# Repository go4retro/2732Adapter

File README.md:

# 2732Adapter
JEDEC 2732 to JEDEC 27XX(X) Adapter

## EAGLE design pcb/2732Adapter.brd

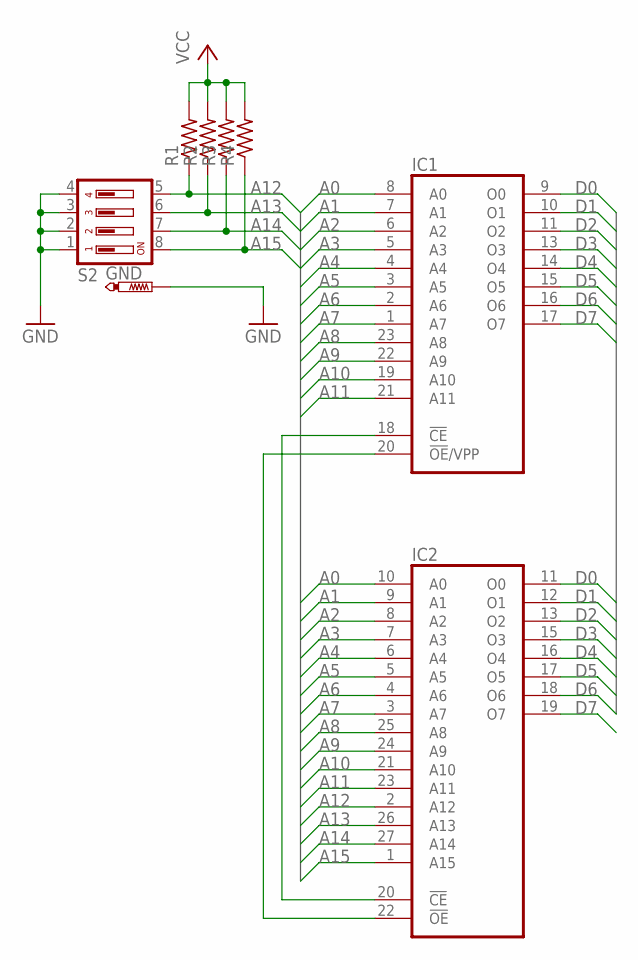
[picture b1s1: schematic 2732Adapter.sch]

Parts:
GND: PTR1B1,27; B1,27
IC1: 2732; DIL24
IC2: 27512; DIL28
R1, R2, R3, R4: R-US_0204/5; 0204/5
S2: DP04; DP-04

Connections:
A0: IC1.8 (A0), IC2.10 (A0)
A1: IC1.7 (A1), IC2.9 (A1)
A2: IC1.6 (A2), IC2.8 (A2)
A3: IC1.5 (A3), IC2.7 (A3)
A4: IC1.4 (A4), IC2.6 (A4)
A5: IC1.3 (A5), IC2.5 (A5)
A6: IC1.2 (A6), IC2.4 (A6)
A7: IC1.1 (A7), IC2.3 (A7)
A8: IC1.23 (A8), IC2.25 (A8)
A9: IC1.22 (A9), IC2.24 (A9)
A10: IC1.19 (A10), IC2.21 (A10)
A11: IC1.21 (A11), IC2.23 (A11)
A12: IC2.2 (A12), R1.1, S2.5
A13: IC2.26 (A13), R2.1, S2.6
A14: IC2.27 (A14), R3.1, S2.7
A15: IC2.1 (A15), R4.1, S2.8
D0: IC1.9 (O0), IC2.11 (O0)
D1: IC1.10 (O1), IC2.12 (O1)
D2: IC1.11 (O2), IC2.13 (O2)
D3: IC1.13 (O3), IC2.15 (O3)
D4: IC1.14 (O4), IC2.16 (O4)
D5: IC1.15 (O5), IC2.17 (O5)
D6: IC1.16 (O6), IC2.18 (O6)
D7: IC1.17 (O7), IC2.19 (O7)
GND: GND.TP, IC1.12 (GND), IC2.14 (GND), S2.1, S2.2, S2.3, S2.4
unnamed: IC1.18 (!CE), IC2.20 (!CE)
unnamed: IC1.20 (!OE!/VPP), IC2.22 (!OE)
VCC: IC1.24 (VCC), IC2.28 (VCC), R1.2, R2.2, R3.2, R4.2

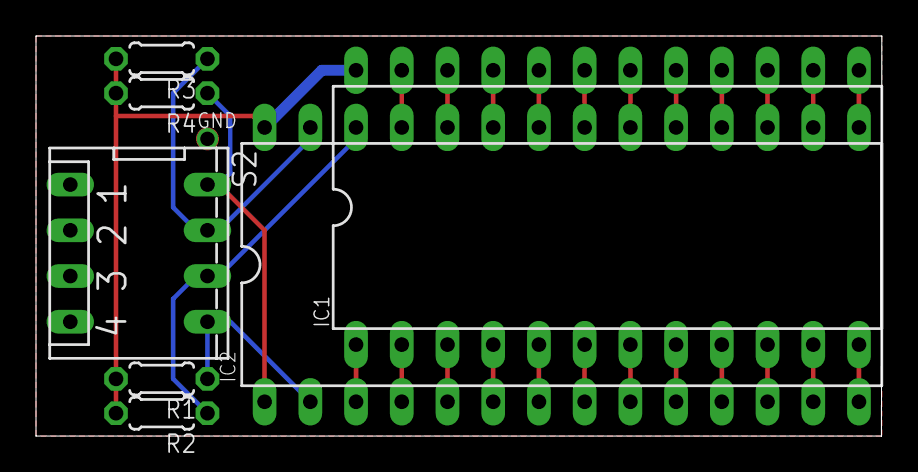
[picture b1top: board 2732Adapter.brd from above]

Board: 2 copper layers, 47.0 x 22.2 mm, 8 parts (0 on the bottom side), 28 nets.

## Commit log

2018-03-11 Updated license
2018-03-11 Added README.md
